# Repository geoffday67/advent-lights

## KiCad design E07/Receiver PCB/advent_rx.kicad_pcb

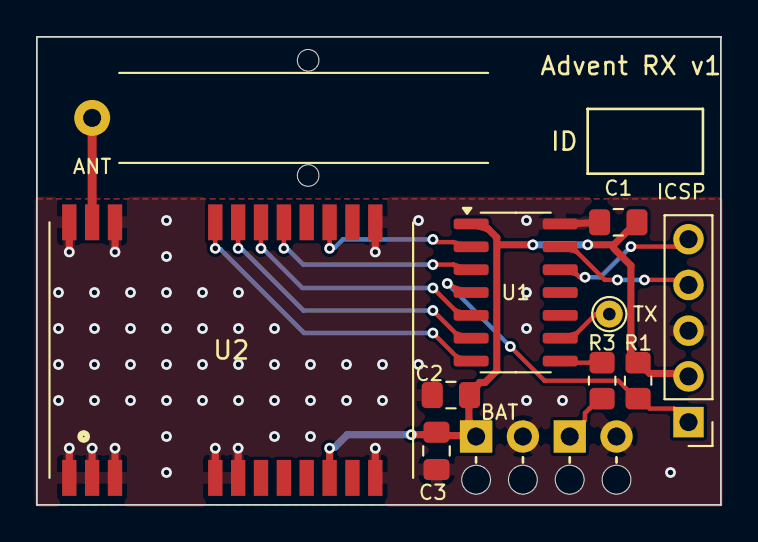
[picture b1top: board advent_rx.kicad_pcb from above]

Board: 2 copper layers, 38.0 x 26.0 mm, 12 parts (0 on the bottom side), 14 nets.

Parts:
AE1: Helical 433MHz; ANT_Helical_433_Placeholder
C1, C3: 100nF; C_0805_2012Metric_Pad1.18x1.45mm_HandSolder
C2: 10uF; C_0805_2012Metric_Pad1.18x1.45mm_HandSolder
J1: ICSP; PinHeader_1x05_P2.54mm_Vertical
J2: BATT; Wire_StrainRelief_1x02_P2.6mm
J3: LED; Wire_StrainRelief_1x02_P2.6mm
R1: 10k; R_0805_2012Metric_Pad1.20x1.40mm_HandSolder
R3: 680; R_0805_2012Metric_Pad1.20x1.40mm_HandSolder
TP1: TX; TestPoint_THTPad_D1.5mm_Drill0.7mm
U1: PIC16F15225-I/SL; SOIC-14_3.9x8.7mm_P1.27mm
U2: E07-400M10S

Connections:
/ANT: AE1.1, U2.21
/CSN: U1.7, U2.19
/GDO2: U1.2, U2.14
/LED_A: J3.1, R3.2
/LED_DRV: R3.1, U1.8
/MCLR: J1.1, R1.2, U1.4
/MISO: U1.3, U2.16
/MOSI: U1.5, U2.17
/PGC: J1.5, U1.12
/PGD: J1.4, U1.13
/SCK: U1.6, U2.18
/UART_TX: TP1.1, U1.9
GND: C1.2, C2.2, C3.2, J1.3, J2.2, J3.2, U1.14, U2.1, U2.2, U2.3, U2.4, U2.5, U2.11, U2.12, U2.20, U2.22
VDD: C1.1, C2.1, C3.1, J1.2, J2.1, R1.1, U1.1, U2.9

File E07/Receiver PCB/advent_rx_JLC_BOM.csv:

Comment,Designator,Footprint,LCSC Part #
100nF,"C1,C3",0805,C49678
10uF,C2,0805,C15850
10k,R1,0805,C17414
E07-400M10S,U2,E07-400M10S (SMD 14x20),C2965513
680,R3,0805,C17798

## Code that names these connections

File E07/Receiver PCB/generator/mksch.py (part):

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    ep.append(pin(n,nm,-15.24,7.62-2.54*k,0,"input" if n in (19,18,17) else "output"))
for k,n in enumerate([1,2,3,4,5,11,12,20,22]):
    ep.append(pin(n,"GND",-10.16+2.54*k,-15.24,90,"power_in"))
ep.append(pin(21,"ANT",15.24,7.62,180,"passive"))
for k,n in enumerate([6,7,8,10,13]):
    ep.append(pin(n,"NC",15.24,2.54-2.54*k,180,"no_connect"))
E07=custom("E07-400M10S","U","E07-400M10S","AdventRX:E07-400M10S",
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part("Device:C","C3","100nF",172.72,63.5,Cf,{1:"VDD",2:"GND"})
part("Device:R","R1","10k",48.26,63.5,R,{1:"VDD",2:"MCLR"})
part("Connector_Generic:Conn_01x05","J1","ICSP (Snap pins 1-5)",43.18,96.52,
     "Connector_PinHeader_2.54mm:PinHeader_1x05_P2.54mm_Vertical",{1:"MCLR",2:"VDD",3:"GND",4:"PGD",5:"PGC"})
part("Connector_Generic:Conn_01x02","J2","Battery 2xAAA (+,-)",43.18,137.16,"AdventRX:Wire_StrainRelief_1x02_P2.6mm",{1:"VDD",2:"GND"})
part("Connector_Generic:Conn_01x02","J3","LED (A,K)",157.48,137.16,"AdventRX:Wire_StrainRelief_1x02_P2.6mm",{1:"LED_A",2:"GND"})
part("Device:R","R3","TBD (LED)",132.08,137.16,R,{1:"LED_DRV",2:"LED_A"})
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
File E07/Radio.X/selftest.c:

/*
 * selftest.c - Startup check of the PIC16F15225's solder joints (both builds).
 *
 * What proves each pin (14-pin package):
 *   1 VDD, 4 MCLR, 12 ICSPCLK, 13 ICSPDAT, 14 VSS   Programming with verify.
 *   9 RC1 (TX, TP1)                                 The log appearing.
 *   8 RC2 (LED / J3)     RX: the LED flash at the end of the test (one long = pass,
 *                        ten short = fail). MODEM: the first command from the controller.
 *   3 RA4 SO, 5 RC5 SI, 6 RC4 SCK                   Write and read back all 256 values.
 *   7 RC3 CSn            A burst write must end when CSn goes high, and GDO1 is
 *                        only visible on SO while CSn is high.
 *   2 RA5 GDO2           GDO2 forced to 0 and to 1.
 *
 * Bridges between adjacent pins:
 *   5-6, 6-7, 7-8, 8-9, 9-10   Pin-pair test, before pins_init().
 *   1-2, 2-3                   GDO1 and GDO2 forced to opposite levels.
 *   3-4, 4-5                   Pin 4 is MCLR (LVP = ON), so a bridge resets the PIC each
 *                              time SO or SI goes low: the log restarts over and over
 *                              with reset cause MCLR.
 *   10-11, 11-12               Not tested: RC0 and RA2 are unused outputs held low, and
 *                              the PIC is held in reset while being programmed, so a
 *                              bridge there does no harm.
 *   12-13, 13-14               Programming fails.
 */

#include "board.h"
#include "uart.h"
#include "radio.h"
#include "selftest.h"

// GDOx_CFG = 0x2F: hardwired to 0; with GDOx_INV (bit 6) set, hardwired to 1
// (CC1101 datasheet Table 41).
#define GDO_HW0     0x2F
#define GDO_INV     0x40

#define RA4_BIT     (1u << 4)           // SO / GDO1
#define RA5_BIT     (1u << 5)           // GDO2

// Adjacent PORTC pins. The 'drive' pin is pulled low while the 'sense' pin is read
// with only its weak pull-up on. RC1 (UART TX) is never driven, so the serial
// adapter sees no break. RC2 is never sensed: in the RX build the LED and R3 hold
// it below the input-high threshold.
static const uint8_t pair_drive[] = { 5, 4, 2, 2, 0 };     // RCn
static const uint8_t pair_sense[] = { 4, 3, 3, 1, 1 };
#define NPAIRS      (sizeof pair_drive / sizeof pair_drive[0])
#define SENSE_MASK  ((1u << 4) | (1u << 3) | (1u << 1))

#define PIN_OF_RC(n)    (10 - (n))      // RC0 = pin 10 ... RC5 = pin 5

static uint8_t reset_cause;             // PCON0 as found at startup
static uint8_t pins_low;                // PORTC bits that read low with only the pull-up on
static uint8_t pairs_bridged;           // Bit i set: pair i bridged
static uint8_t failures;

void selftest_pins(void) {
    reset_cause = PCON0;
    PCON0 = 0x1F;                       // STKOVF = STKUNF = 0; RWDT, RMCLR, RI, POR, BOR = 1

    // Reset state: all pins inputs, analog. Make PORTC digital inputs with pull-ups.
    ANSELC = 0x00;
    LATC   = 0x00;                      // A pin made an output drives low
    WPUC   = 0x3F;
    TRISC  = 0x3F;
    __delay_us(100);

    pins_low = (uint8_t)(~PORTC & SENSE_MASK);
    pairs_bridged = 0;
    for (uint8_t i = 0; i < NPAIRS; i++) {
        uint8_t drive = (uint8_t)(1u << pair_drive[i]);
        uint8_t sense = (uint8_t)(1u << pair_sense[i]);
        if (pins_low & sense) {
            continue;                   // Already reported as low
        }
        TRISC &= (uint8_t)~drive;
        __delay_us(20);
        if (!(PORTC & sense)) {
            pairs_bridged |= (uint8_t)(1u << i);
        }
        TRISC |= drive;
        __delay_us(20);
    }

    WPUC = 0x00;                        // pins_init() sets the working directions and pull-ups
}

static void fail(const char *msg) {
    uart_puts("  FAIL ");
    uart_puts(msg);
    uart_puts("\r\n");
    failures++;
}

static void put_reset_cause(void) {
    uart_puts("Reset cause: ");
    if (!(reset_cause & 0x02)) {
        uart_puts("power-on");
    } else if (!(reset_cause & 0x08)) {
        uart_puts("MCLR (pin 4)");
    } else if (reset_cause & 0xC0) {
        uart_puts("stack over/underflow");
    } else if (!(reset_cause & 0x04)) {
        uart_puts("RESET instruction");
    } else if (!(reset_cause & 0x10)) {
        uart_puts("watchdog");
    } else {
        uart_puts("other");
    }
    uart_puts(" (PCON0 ");
    uart_puthex(reset_cause);
    uart_puts(")\r\n");
}

static void radio_tests(void) {
    if (!radio_reset()) {
        fail("radio: SO did not go low with CSn low (pin 7 RC3 CSn, pin 3 RA4 SO)");
        return;
    }

    // 1. SPI data path: every value written to FREQ1 (all 8 bits R/W) and read back.
    uint16_t bad = 0;
    for (uint16_t v = 0; v < 256; v++) {
        radio_write_reg(CC1101_FREQ1, (uint8_t)v);
        if (radio_read_reg(CC1101_FREQ1) != (uint8_t)v) {
            bad++;
        }
    }
    if (bad) {
        uart_puts("  FAIL SPI: ");
        uart_putdec((int16_t)bad);
        uart_puts(" of 256 values read back wrong (pin 3 RA4 SO, pin 5 RC5 SI, pin 6 RC4 SCK)\r\n");
        failures++;
        return;                         // The tests below need a working SPI link
    }

    // 2. CSn: a burst write only ends when CSn goes high. If CSn stays low at the
    //    radio, the single write and reads that follow are taken as more burst data.
    //    Single accesses work without CSn going high, so test 1 does not catch this.
    static const uint8_t pattern[2] = { 0xA5, 0x5A };
    radio_write_burst(CC1101_FREQ1, pattern, 2);        // FREQ1, FREQ0
    radio_write_reg(CC1101_PKTLEN, 0xC3);
    uint8_t f1 = radio_read_reg(CC1101_FREQ1);
    uint8_t f0 = radio_read_reg(CC1101_FREQ0);
    uint8_t pl = radio_read_reg(CC1101_PKTLEN);
    if (f1 != 0xA5 || f0 != 0x5A || pl != 0xC3) {
        fail("CSn: burst write did not end, so CSn is not going high at the radio (pin 7 RC3)");
    }

    // 3. GDO1 and GDO2 forced to opposite levels, read with CSn high. SO carries
    //    GDO1 only while CSn is high (datasheet Section 11.2), so with test 1 passed
    //    a wrong GDO1 level means CSn is not going high. The RA5 pull-up makes an
    //    open GDO2 joint read 1.
    WPUAbits.WPUA5 = 1;
    radio_write_reg(CC1101_IOCFG1, GDO_HW0);
    radio_write_reg(CC1101_IOCFG2, GDO_HW0 | GDO_INV);
    __delay_us(20);
    uint8_t a = PORTA;                  // Expect RA4 = 0, RA5 = 1
    radio_write_reg(CC1101_IOCFG1, GDO_HW0 | GDO_INV);
    radio_write_reg(CC1101_IOCFG2, GDO_HW0);
    __delay_us(20);
    uint8_t b = PORTA;                  // Expect RA4 = 1, RA5 = 0
    WPUAbits.WPUA5 = 0;

    uint8_t so_ok   = !(a & RA4_BIT) &&  (b & RA4_BIT);
    uint8_t gdo2_ok =  (a & RA5_BIT) && !(b & RA5_BIT);
    uint8_t same_a  = ((a & RA4_BIT) != 0) == ((a & RA5_BIT) != 0);
    uint8_t same_b  = ((b & RA4_BIT) != 0) == ((b & RA5_BIT) != 0);
    if (!so_ok && !gdo2_ok && same_a && same_b) {
        fail("pins 2 and 3 bridged (RA5 GDO2 and RA4 SO always read the same)");
    } else {
        if (!gdo2_ok) {
            fail("GDO2 not seen on pin 2 (RA5): open joint, or bridged to pin 1 (VDD)");
        }
        if (!so_ok) {
            fail("GDO1 not seen on SO with CSn high: CSn not going high at the radio (pin 7 RC3)");
        }
    }

    radio_reset();                      // Back to reset values before the real configuration
}

uint8_t selftest_run(void) {
    failures = 0;

    put_reset_cause();
    uart_puts("Self-test:\r\n");

    for (uint8_t n = 0; n < 6; n++) {
        if (pins_low & (1u << n)) {
            uart_puts("  FAIL pin ");
            uart_putdec(PIN_OF_RC(n));
            uart_puts(" (RC");
            uart_putdec(n);
            uart_puts(") reads low with only its pull-up: shorted to GND\r\n");
            failures++;
        }
    }
    for (uint8_t i = 0; i < NPAIRS; i++) {
        if (pairs_bridged & (1u << i)) {
            uart_puts("  FAIL pins ");
            uart_putdec(PIN_OF_RC(pair_drive[i]));
            uart_puts(" and ");
            uart_putdec(PIN_OF_RC(pair_sense[i]));
            uart_puts(" bridged (RC");
            uart_putdec(pair_drive[i]);
            uart_puts(", RC");
            uart_putdec(pair_sense[i]);
            uart_puts(")\r\n");
            failures++;
        }
    }

    radio_tests();

    if (failures == 0) {
        uart_puts("  PASS\r\n");
    } else {
        uart_puts("  ");
        uart_putdec(failures);
        uart_puts(" failure(s)\r\n");
    }

#if defined(ROLE_RX)
    // Pin 8 check by eye: one 200 ms flash = pass, ten short flashes = fail.
    if (failures == 0) {
        LED = 1;
        __delay_ms(200);
        LED = 0;
    } else {
        for (uint8_t i = 0; i < 10; i++) {
            LED = 1;
            __delay_ms(50);
            LED = 0;
            __delay_ms(50);
        }
    }
#endif

    return failures;
}
